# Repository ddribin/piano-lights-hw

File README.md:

# Piano Lights Hardware

Specialized hardware to displays lights (LEDs) over piano keys.

See a [demo video on YouTube](https://youtu.be/pe3vuLcroIA).

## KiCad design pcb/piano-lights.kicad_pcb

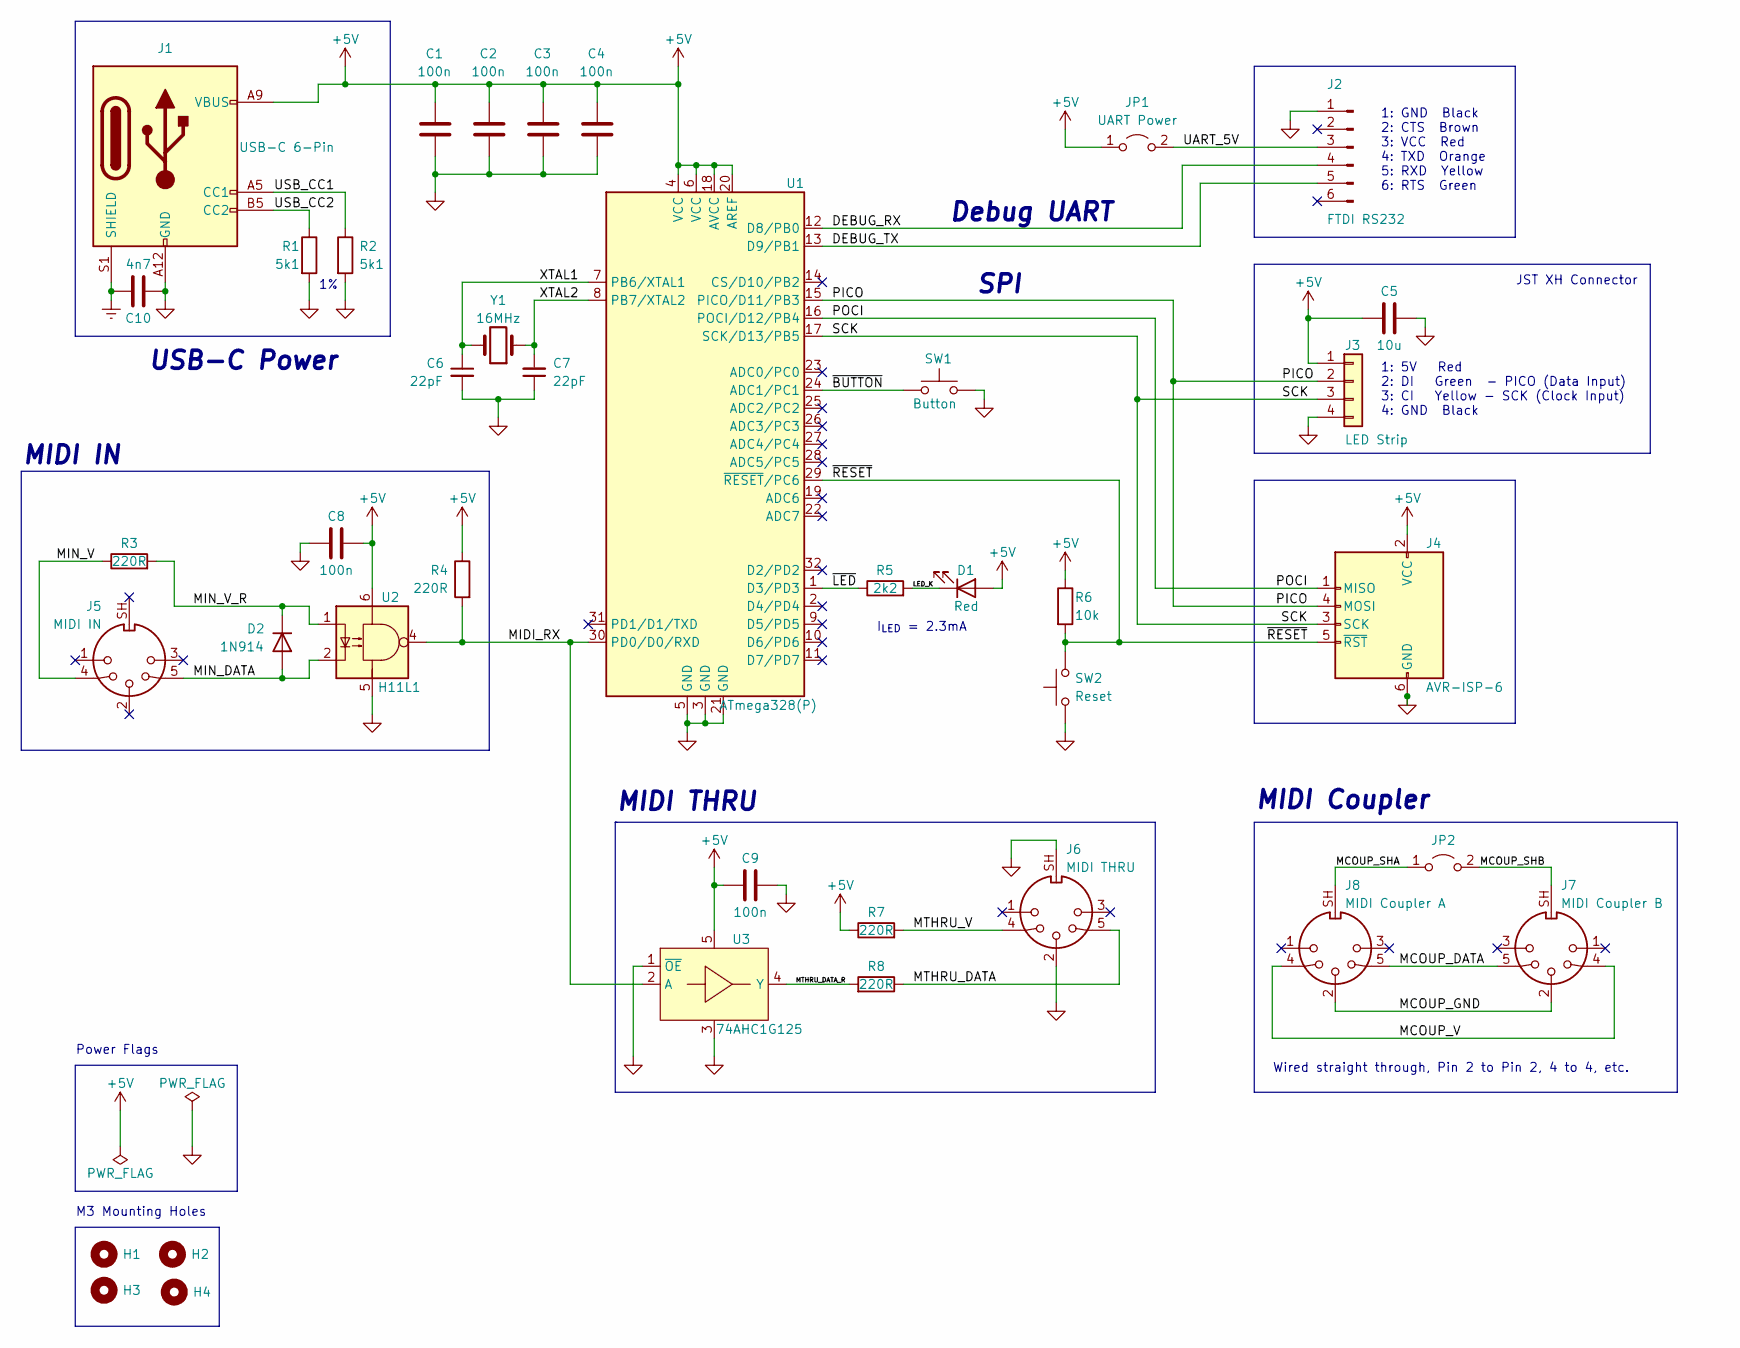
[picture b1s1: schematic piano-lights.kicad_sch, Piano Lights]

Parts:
C1, C2, C3, C4, C8, C9: 100n; C_0603_1608Metric_Pad1.08x0.95mm_HandSolder; Mfr Part GRM188R72A104KA35D
C5: 10u; CP_Radial_D5.0mm_P2.00mm; Mfr Part UVR1C100MDD
C6, C7: 22pF; C_0603_1608Metric_Pad1.08x0.95mm_HandSolder; Mfr Part GCM1885C2A220JA16D
C10: 4n7; C_0805_2012Metric_Pad1.18x1.45mm_HandSolder; Mfr Part GRM2165C1H472JA01D
D1: Red; LED_0603_1608Metric_Pad1.05x0.95mm_HandSolder; Mfr Part SML-D12U8WT86
D2: 1N914; D_SOD-123; Mfr Part MMSD4148T1G
H1, H2, H3, H4: MountingHole; MountingHole_3.2mm_M3
J1: USB-C 6-Pin; GCT_USB4125-GF-A-0190_REVA2; Mfr Part USB4125-GF-A-0190
J2: FTDI RS232; PinHeader_1x06_P2.54mm_Vertical
J3: LED Strip; JST_XH_S4B-XH-A_1x04_P2.50mm_Horizontal
J4: AVR-ISP-6; PinHeader_2x03_P2.54mm_Vertical; Mfr Part PR20203VBDN
J5: MIDI IN; CUI_SDS-50J; Mfr Part SDS-50J
J6: MIDI THRU; CUI_SDS-50J; Mfr Part SDS-50J
J7: MIDI Coupler B; CUI_SDS-50J; Mfr Part SDS-50J
J8: MIDI Coupler A; CUI_SDS-50J; Mfr Part SDS-50J
JP1: UART Power; PinHeader_1x02_P2.54mm_Vertical
JP2: MIDI Coupler Shield; PinHeader_1x02_P2.54mm_Vertical
R1, R2: 5k1; R_0603_1608Metric_Pad0.98x0.95mm_HandSolder; Mfr Part RC0603FR-075K1L
R3, R4, R7, R8: 220R; R_0603_1608Metric_Pad0.98x0.95mm_HandSolder; Mfr Part RC0603JR-07220RL
R5: 2k2; R_0603_1608Metric_Pad0.98x0.95mm_HandSolder; Mfr Part RC0603JR-072K2L
R6: 10k; R_0603_1608Metric_Pad0.98x0.95mm_HandSolder; Mfr Part RC0603JR-0710KL
SW1: Button; SW_PUSH_6mm_H5mm; Mfr Part CT11025.0F160
SW2: Reset; SW_PUSH_6mm_H5mm; Mfr Part CT11025.0F160
U1: ATmega328(P); TQFP-32_7x7mm_P0.8mm; Mfr Part ATMEGA328-AUR
U2: H11L1; SMDIP-6_W9.53mm; Mfr Part H11L1M
U3: 74AHC1G125; SOT-23-5_HandSoldering; Mfr Part 74AHC1G125GV,125
Y1: 16MHz; Crystal_HC49-U_Vertical; Mfr Part ECS-160-18-4X-CKM

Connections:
+5V: C1.1, C2.1, C3.1, C4.1, C5.1, C8.2, C9.1, D1.2 (A), J1.A9 (VBUS), J1.B9 (VBUS), J3.1, J4.2 (VCC), JP1.1 (A), R4.1, R6.1, R7.1, U1.4 (VCC), U1.6 (VCC), U1.18 (AVCC), U1.20 (AREF), U2.6, U3.5
/DEBUG_RX: J2.4, U1.12 (D8/PB0)
/DEBUG_TX: J2.5, U1.13 (D9/PB1)
/LED_K: D1.1 (K), R5.2
/MCOUP_DATA: J7.5, J8.5
/MCOUP_GND: J7.2, J8.2
/MCOUP_SHA: J8.SH, JP2.1 (A)
/MCOUP_SHB: J7.SH, JP2.2 (B)
/MCOUP_V: J7.4, J8.4
/MIDI_RX: R4.2, U1.30 (PD0/D0/RXD), U2.4, U3.2 (A)
/MIN_DATA: D2.2 (A), J5.5, U2.2
/MIN_V: J5.4, R3.1
/MIN_V_R: D2.1 (K), R3.2, U2.1
/MTHRU_DATA: J6.5, R8.1
/MTHRU_DATA_R: R8.2, U3.4 (Y)
/MTHRU_V: J6.4, R7.2
/PICO: J3.2, J4.4 (MOSI), U1.15 (PICO/D11/PB3)
/POCI: J4.1 (MISO), U1.16 (POCI/D12/PB4)
/SCK: J3.3, J4.3 (SCK), U1.17 (SCK/D13/PB5)
/UART_5V: J2.3, JP1.2 (B)
/USB_CC1: J1.A5 (CC1), R2.1
/USB_CC2: J1.B5 (CC2), R1.1
/XTAL1: C6.1, U1.7 (PB6/XTAL1), Y1.2
/XTAL2: C7.2, U1.8 (PB7/XTAL2), Y1.1
/~BUTTON: SW1.1, U1.24 (ADC1/PC1)
/~LED: R5.1, U1.1 (D3/PD3)
/~RESET: J4.5 (~RST), R6.2, SW2.2, U1.29 (~RESET/PC6)
Earth: C10.2, J1.S1 (SHIELD)
GND: C1.2, C2.2, C3.2, C4.2, C5.2, C6.2, C7.1, C8.1, C9.2, C10.1, J1.A12 (GND), J1.B12 (GND), J2.1, J3.4, J4.6 (GND), J6.2, J6.SH, R1.2, R2.2, SW1.2, SW2.1, U1.3 (GND), U1.5 (GND), U1.21 (GND), U2.5, U3.1 (~OE), U3.3

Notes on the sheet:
1: GND Black 2: CTS Brown 3: VCC Red 4: TXD Orange 5: RXD Yellow 6: RTS Green
MIDI THRU
Debug UART
1: 5V Red 2: DI Green - PICO (Data Input) 3: CI Yellow - SCK (Clock Input) 4: GND Black
Wired straight through, Pin 2 to Pin 2, 4 to 4, etc.
JST XH Connector
I_{LED} = 2.3mA
USB-C Power
MIDI IN
SPI
MIDI Coupler
Power Flags
M3 Mounting Holes

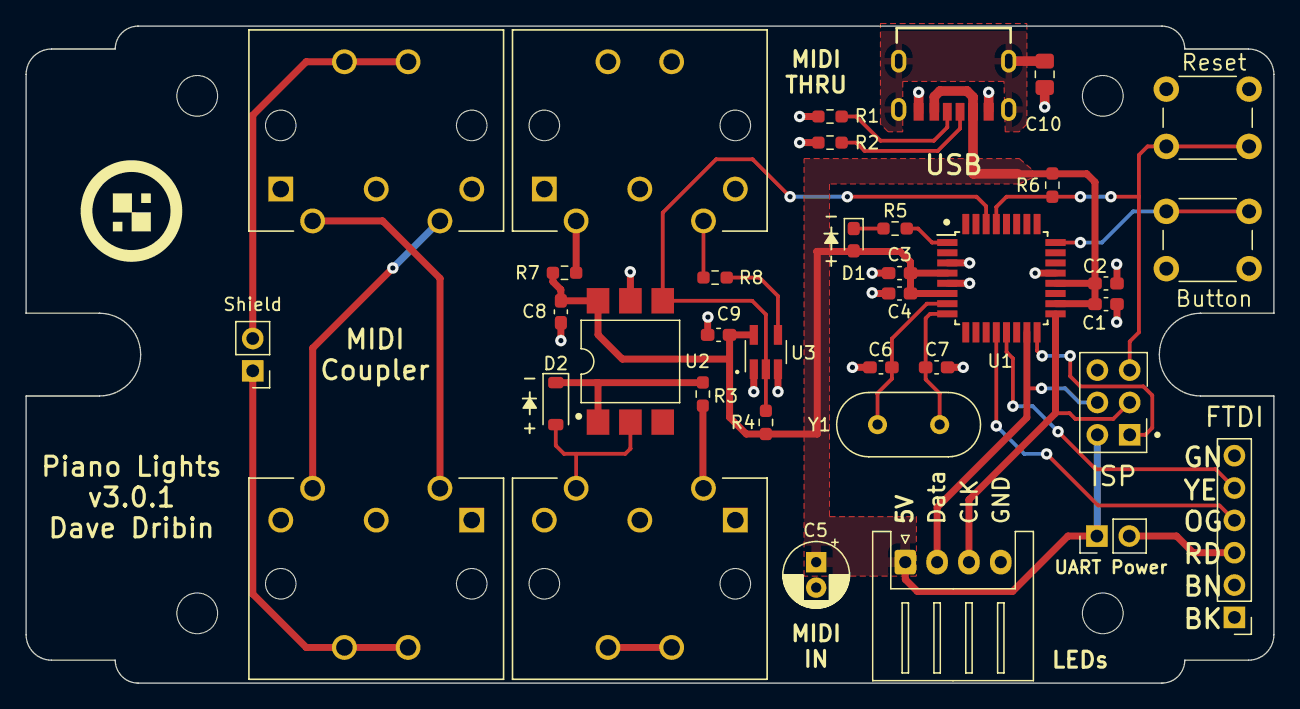
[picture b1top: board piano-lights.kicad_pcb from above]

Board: 2 copper layers, 98.0 x 51.6 mm, 41 parts (0 on the bottom side), 29 nets.

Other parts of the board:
G1: LOGO

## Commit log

2022-06-04 Flesh out circuit
2022-06-04 Add debug port and more net labels
2022-06-08 Restructure the schematic and start adding footprints
2022-06-09 Finish footprints. Start laying out PCB.
2022-06-09 More PCB updates
2022-06-10 Start the board layout
2022-06-18 PCB updates
2022-06-19 Start re-working schematic (again)
2022-06-19 Finish reworking schematic
2022-06-19 Renumber components, and start over on the PCB.
2022-06-19 Update 74AHC1G125 symbol so that VCC and GND are at the top and bottom, respectively
2022-06-19 Minor schematic and PCB updates
2022-06-19 Move reset switch
2022-06-19 Move LED to D7/PD7
2022-06-19 Fix misaligned POCI wire
2022-06-19 Add in a switch on D2/PD2. Move MIDI_RX to the left side.
2022-06-19 Clean up MIDI IN and THRU. Rename shield pin on the DIN5 connector to match the conventions.
2022-06-20 Add some 3D models and start laying out PCB (it's too small, though)
2022-06-21 Start laying out PCB
2022-06-22 Tweeak dimensions. Move LED connector to other side, closer to USB power.
2022-06-22 Fully route board. Does not pass DRC, yet.
2022-06-22 Fix up copper pours power puddles on the front
2022-06-22 PCB tweaks
2022-06-25 Fix up silk screen. Fix all DRC errors. Tweak position of LED holes.
2022-06-26 Add a cutout in the side.
2022-06-26 Add some more silk screen info
2022-06-26 Minor trace tweaks. Move origin to center.
2022-06-26 Clean up somem more tracks and passive placement
2022-06-26 Update version text and date.
2022-06-26 Add a jumper for 5V UART power. Add more silk.
2022-06-26 Final tweaks
2022-06-27 Tweak silkscreen
2022-06-27 Make the hole wider
2022-06-30 Last minue DRC updates for JLCPCB
2022-06-30 Update solder mask DRC
2022-07-16 Add CHANGELOG.md
2022-07-16 CHANLOGE.md: Update link to v1.0.0
2022-07-16 CHANLOGE.md: Update link to compare v1.0.0
2022-07-16 Get the dang compare link correct
2022-07-17 Mock up fixes for reversed H11L1 inputs and pull-up
2022-07-18 Clean up schematic mainly around MIDI IN
2022-07-18 Switch MIDI IN diode footprint to MiniMELF
    - Add some more silkscreen around AVR ISP-6 header.
    - Add silscreen text for USB Power.
2022-07-18 Fix DRC issues
2022-07-18 Minor reroutes around MIDI IN
2022-07-22 Silkscreen updates
2022-08-07 Minor re-routing
2022-08-07 Add some test points
2022-08-07 Update plot settings for JLCPCB
2022-08-08 Update solder mask constraints to allow solder mask between USB connector pads
    - Update some JLCPCB constraints.
    - Update front copper pours to be right angles.
2022-08-08 Add license and readme
2022-08-08 Update changelog to reference Issue #5
2022-08-08 Add links to issues in changelog
2022-08-08 Fix link to v1.0.1 in changelog
2022-08-08 Fix typo in changelog
2022-08-08 Move gerbers/ ignore to pcb/.gitignore
2022-08-08 Update links to issues
2022-08-12 Put component values on silkscreen
2022-08-12 More silkscreen updates
2022-08-12 Update changelog
2022-08-12 Update dates
2022-08-12 Add InteractiveHtmlBom (ibom) configuration
2022-08-12 Update ibom config
2023-02-09 First pass at smaller PCB with MIDI coupler
2023-02-09 Fix up schematic, update to SMD CPU, and start laying out board
2023-02-10 More PCB routing
2023-02-10 Finish first pass of routing: no more unrouted nets. It fits!
2023-02-11 Cleanup MIDI coupler wiring a bit
2023-02-11 More routing updates
2023-02-13 Update track widths
2023-02-13 Add the button back, but on a different pin. Start cleaning up silkscreen
2023-02-13 Finish cleaning up silkscreen. Passes DRC. Add dimensions.
2023-02-13 Last silkscreen tweaks
2023-02-13 Reroute /LED signal away from the crystal
2023-02-13 Move /LED to Pin 1 for easier PCB routing
2023-02-13 Update silkscreen for LED strip
2023-02-13 Add silkscreen for all RS323/FTDI pins
2023-02-13 More siklscreen tweaks
2023-02-13 Simplify power distribution a bit
2023-02-16 Start adding mfr, part, and vendor to schematic
2023-02-16 Add more Mfr notes
2023-02-16 Add more Mfr comments. Switch to SMD 0805 LED
2023-02-16 Update footprint of USB connector
2023-02-16 Add logo on PCB silkscreen
2023-02-16 Update revision and date
2023-02-18 Add USB-C Power only connector footprint for GCT USB4125-GF-A-0190.
2023-02-18 Switch to USB-C 6-Pin for power on the schematic
2023-02-18 Start wiring up USB-C connector
2023-02-18 Route out +5V to the LEDs with a copper pour
2023-02-18 Widden +5V copper pour to 2mm
2023-02-18 Increase Power net class width to 0.55mm
2023-02-18 Make via sizes larger at 0.4mm drill and 0.9mm diameter. Fix resulting DRC errors.
2023-02-18 Make longer pads on USB-C connector
2023-02-18 Remove some extra silkscreen
2023-02-18 Tweak hole clearances
2023-02-18 Fix DRC errors and pull back the soldermask expansion to 0.0508
2023-02-18 Move USB-C connector over to the left a bit to make room for a resistor on the right
2023-02-18 Make FTDI power trace thicker (1.6mm)
2023-02-18 Align some schematic components to 0.050in grid
2023-02-18 Minre schematic tweaks
2023-02-18 Swap J1 and J2 designators so J1 is at the upper left
2023-02-18 Minor PCB tweaks
2023-02-18 Use copper pour instead of thick traces, to get thermal reliefs around through holes
2023-02-19 Set Mfr, Mfr Part, and Vendor on most other components
2023-02-19 Clean up MIDI coupler schematic a bit
2023-02-19 Clean up ERC and DRC issues
2023-02-19 Simplify MIDI coupler by mirroring the second connector horizontally
2023-02-19 More schematic cleanups
2023-02-19 Move R8 a bit away from the copper pour
2023-02-19 Move U3 a bit away from the copper pour
2023-02-19 Make LED data and clock thicker traces
2023-02-19 Increase padding around KiBuzzard labels to 5mm
2023-02-19 Tigthen up ground pour around board outline
2023-02-19 Cleanup SCK track a bit
2023-02-19 Fill in part data for crystal
2023-02-19 Rearrange R7 and C8
2023-02-19 Move C9 closer to U3. Fix DRC errors.
2023-02-20 Minor tweaks
2023-02-20 Fill out Mfr fields for last capacitor in the schematic
2023-02-21 Add a jumper on the coupler shield
2023-02-21 Bump clearance to 0.2mm (from 0.19mm)
2023-02-21 Add a dot to H11L1 and slightly adjust the Button trace
2023-02-21 Make button signl active low
2023-02-22 Start fleshing out changelog
2023-02-22 Add more dimensions in PCB to ensure they match the enclosure
2023-02-22 Futz around with outline on the User.2 layer
2023-02-22 In schematic, rename 'Button' signal to 'BUTTON' to be consistent with other signals
2023-02-23 Tweak copper pours again. Make sure all of them are consistent
2023-02-23 Update changelog and dates on the sheets
2023-02-23 Increase +5V power plan thermal relief spokes to 0.76mm
2023-02-23 Update output directories when plotting
2023-02-23 Update Unreleased link in the changelog
2023-02-23 Minor tweaks to changelog
2023-02-23 Add an "R" suffix to the 220 ohm resistors
2023-03-06 Switch to SOD-123 package for diode #6
2023-03-06 Switch to SMD part of H11L1 #2
2023-03-06 Minor layout tweaks
2023-03-06 Switch to SMD pushbutton switches #9
2023-03-06 Revert "Switch to SMD pushbutton switches #9"
    This reverts commit b74edbcdb394744f791cc2b63e3a5d736e74cc88.
2023-03-06 Fix up left ground plane that got moved
2023-03-06 Move GND via of H11L1 underneath the chip
2023-03-06 Change FTDI +5V trace to a normal power trace, instead of copper pour #10
2023-03-06 Switch LED strip to JST XH right angle connector #8
2023-03-09 First attempt at MIDI IN faceplate
2023-03-12 Tweak MIDI ports to match PCB
2023-03-12 Add a faceplate for the MIDI OUT side
2023-03-13 Update MIDI IN faceplate a bit
2023-03-13 Upgrade PCB to KiCad v7 file format
2023-03-13 Replace KiBuzzard text with new KiCad 7 custom font text
2023-03-13 Tweak positions of MIDI connectors to be exactly aligned
2023-03-13 Upgrade schematic file format to KiCad v7
2023-03-13 Use a real monospace font (Menlo) for parts of schematic
2023-03-13 Fix new ERC errors (mostly grid issues, with some symbol updates)
2023-03-13 Switch to 0603 package for LED #7
2023-03-13 Fix up diode footprint
2023-03-16 Fill in metadata and put version number (v2.1.0b1) on the back silkscreen
2023-03-16 Rename faceplate files to use dashes instead of underscores
2023-03-16 More file renaming
2023-03-16 Add dimensions
2023-06-11 Move USB and LED ports so they overhang by 1mm
2023-06-11 Update USB and LED connector footprints so that silkscreen does not overhang the board
2023-06-11 Update LED port silkscreen and placement to fix DRC errors
2023-06-11 Hookup USB shield to Earth and add a capacitor between Earth and GND
2023-06-11 Start expanding board
2023-06-11 Expand board out 1.8mm on the top and bottom
2023-06-11 Better align one of the +5V copper pours
2023-06-20 Tie USB-C shield to earth and add a 4n7F cap between earth and ground
2023-06-21 Reroute CC1 and CC2 to not cross ground split planes. Move Earth to front ground pour.
2023-06-27 Rarrange CC1 and CC2 resistors to be next to each other
2023-06-27 Silkscreen tweaks
2023-06-27 Move C5 down a bit, so it aligns with the connector
2023-06-27 Move R1 and R2 again
2023-06-27 Rotate C1 and C2
2023-06-27 Reroute +5V to C1 and C2
2023-06-27 Tweak Reset trace
2023-06-27 Update CHANGELOG.md
    Minor PCB tweaks
2023-06-29 Switch Earth to GND capacitor to 0803 (from 0603)
2023-07-03 Update offset around JST connector to 0.2mm (from 0.1mm)
    Update version numbers to 3.0.0
2023-07-03 Update faceplates
2023-07-04 Update all versions to 3.0.0 and update date
2023-07-05 Update CHANGELOG and update release date
2023-07-05 Update PCB from schematic
2023-07-28 Fix reversed silkscreen on LED D1 #13
2023-07-28 Add text about JST XH connector on schematic
2023-08-04 Zone refile for gerbers
2023-08-04 Fix DRC warning on the graphic, by ignoring it
2023-08-04 Fix SPICE ERC error by ignoring it
2023-08-04 Fix CHANGELOG typos
2023-12-01 .gitignore: Add KiCad lock files
2024-11-21 Add a comment about the 0.2mm offset
